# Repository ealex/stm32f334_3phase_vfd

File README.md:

# stm32f334_3phase_vfd
stm32f334 3 phase variable frequency drive with STGIB15CH60TS-L module

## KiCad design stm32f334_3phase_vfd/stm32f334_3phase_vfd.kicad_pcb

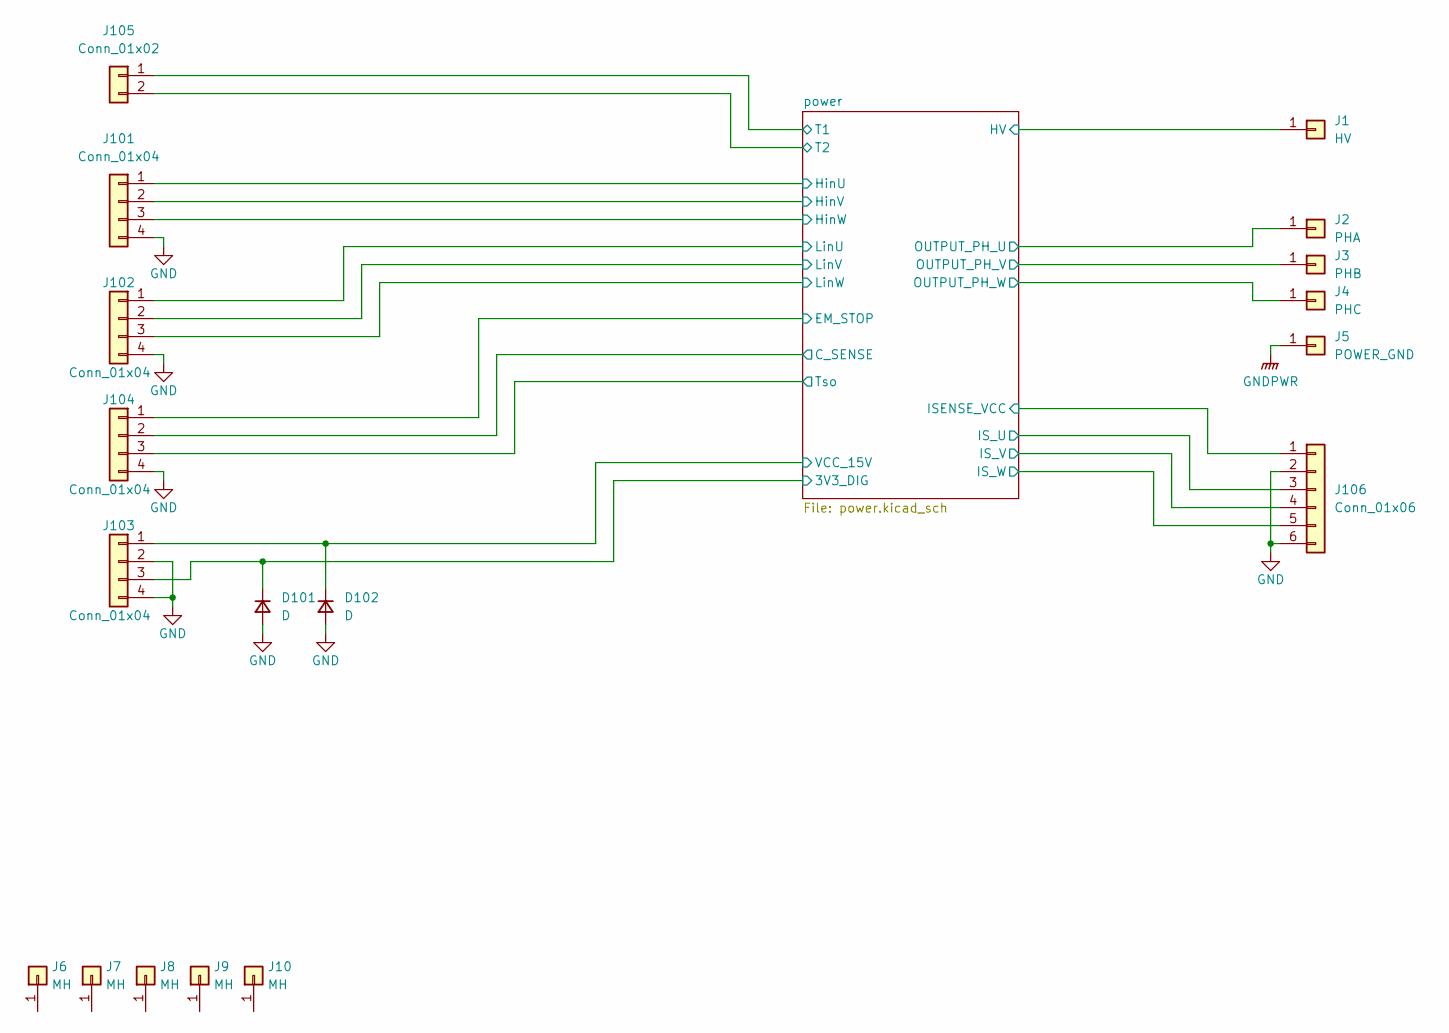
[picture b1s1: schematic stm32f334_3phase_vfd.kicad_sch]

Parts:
D101, D102: D; D_SMA
J1: HV; KEYSTONE_7788
J2: PHA; KEYSTONE_7788
J3: PHB; KEYSTONE_7788
J4: PHC; KEYSTONE_7788
J5: POWER_GND; KEYSTONE_7788
J6, J7, J8, J9, J10: MH; MountingHole_3.2mm_M3_Pad_TopBottom
J101, J102, J103, J104: Conn_01x04; JST_PH_B4B-PH-K_1x04_P2.00mm_Vertical
J105: Conn_01x02; JST_PH_B2B-PH-K_1x02_P2.00mm_Vertical
J106: Conn_01x06; JST_PH_B6B-PH-K_1x06_P2.00mm_Vertical

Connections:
/power/3V3_DIG: D101.1 (K), J103.3; also elsewhere on the board
/power/Cin: J104.2; also elsewhere on the board
/power/HV: J1.1; also elsewhere on the board
/power/HinU: J101.1; also elsewhere on the board
/power/HinV: J101.2; also elsewhere on the board
/power/HinW: J101.3; also elsewhere on the board
/power/ISENSE_VCC: J106.1; also elsewhere on the board
/power/IS_U: J106.3; also elsewhere on the board
/power/IS_V: J106.4; also elsewhere on the board
/power/IS_W: J106.5; also elsewhere on the board
/power/LinU: J102.1; also elsewhere on the board
/power/LinV: J102.2; also elsewhere on the board
/power/LinW: J102.3; also elsewhere on the board
/power/T1: J105.1; also elsewhere on the board
/power/T2: J105.2; also elsewhere on the board
/power/Tso: J104.3; also elsewhere on the board
/power/U: J2.1; also elsewhere on the board
/power/V: J3.1; also elsewhere on the board
/power/VCC_15V: D102.1 (K), J103.1; also elsewhere on the board
/power/W: J4.1; also elsewhere on the board
/power/~sd_od: J104.1; also elsewhere on the board
GND: D101.2 (A), D102.2 (A), J101.4, J102.4, J103.2, J103.4, J104.4, J106.2, J106.6; also elsewhere on the board
GNDPWR: J5.1; also elsewhere on the board

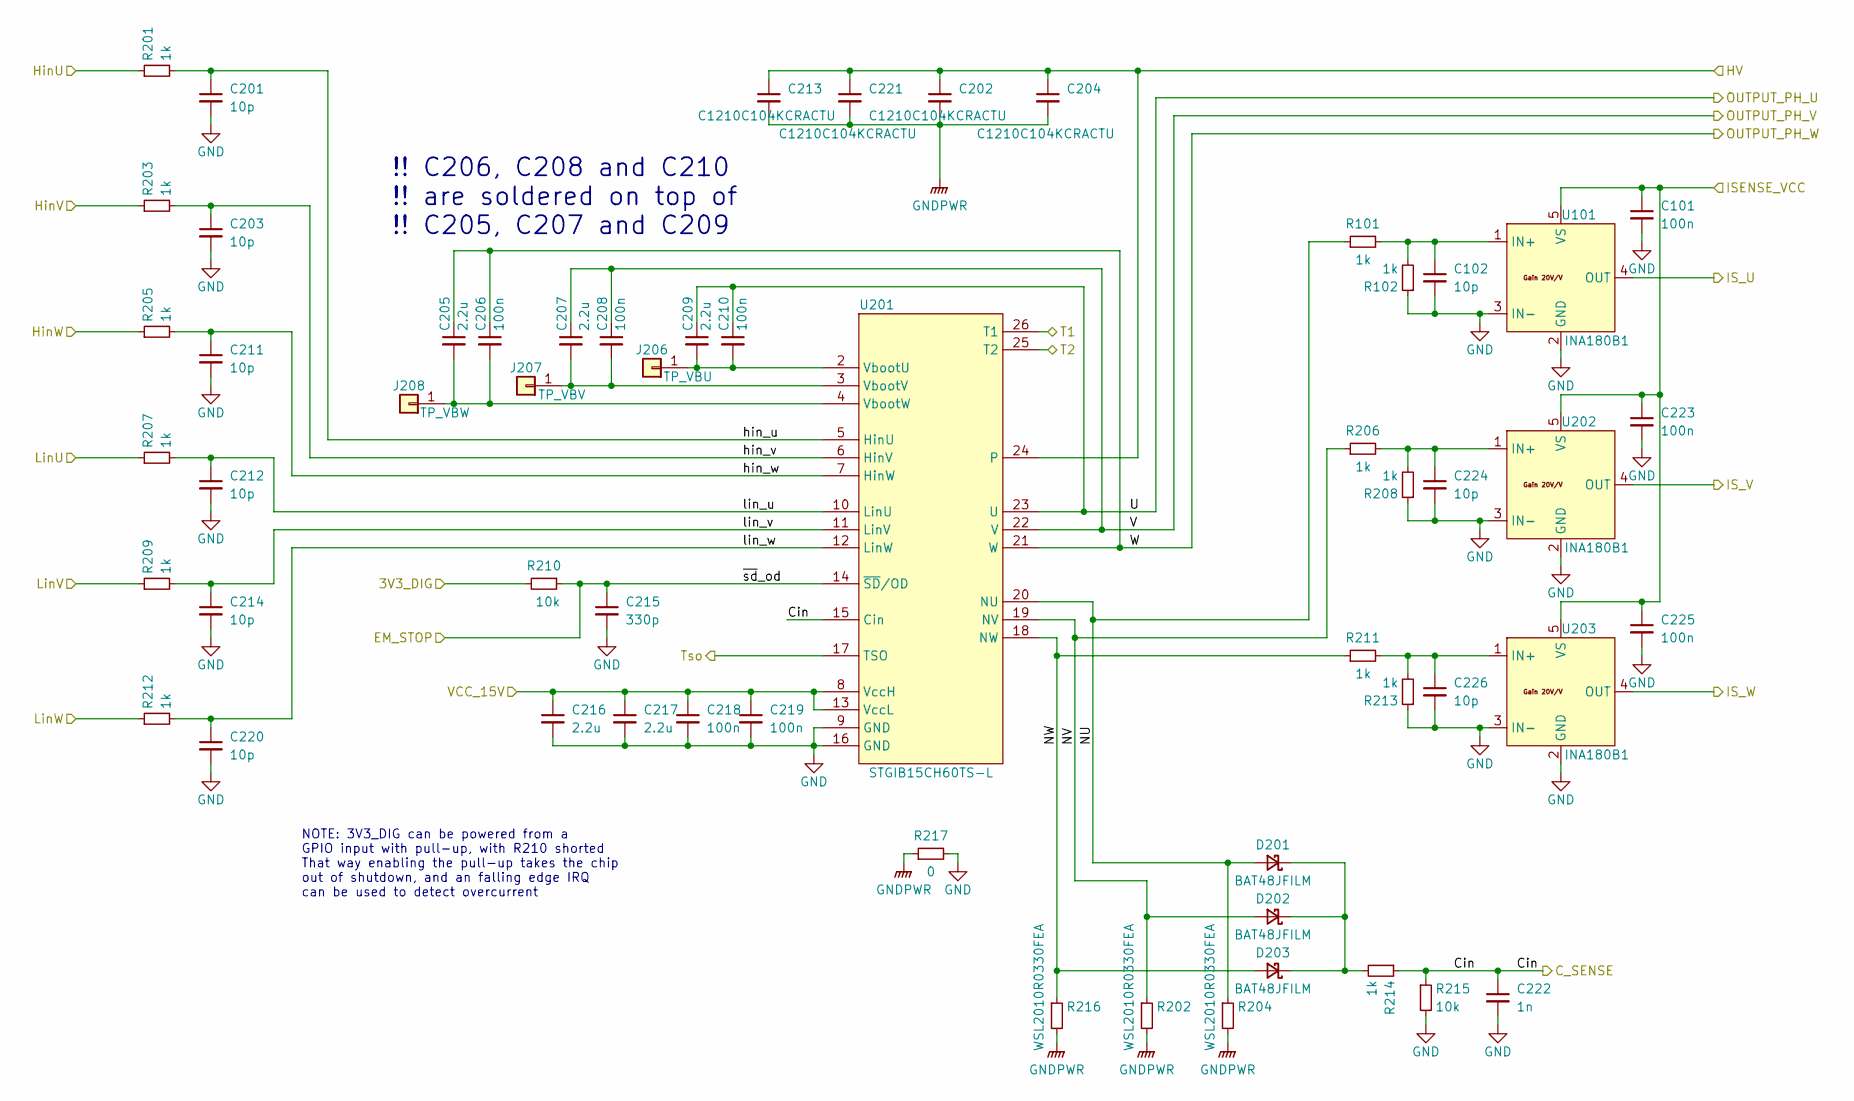
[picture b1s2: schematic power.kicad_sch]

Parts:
C101, C218, C219, C223, C225: 100n; C_0805_2012Metric
C102, C201, C203, C211, C212, C214, C220, C224, C226: 10p; C_0805_2012Metric
C202, C204, C213, C221: C1210C104KCRACTU; C_1210_3225Metric
C205, C207, C209, C216, C217: 2.2u; C_1206_3216Metric
C206, C208, C210: 100n; C_1206_3216Metric
C215: 330p; C_0805_2012Metric
C222: 1n; C_0805_2012Metric
D201, D202, D203: BAT48JFILM; D_SOD-323
J206: TP_VBU; PinHeader_1x01_P2.54mm_Vertical
J207: TP_VBV; PinHeader_1x01_P2.54mm_Vertical
J208: TP_VBW; PinHeader_1x01_P2.54mm_Vertical
R101, R102, R201, R203, R205, R206, R207, R208, R209, R211, R212, R213, R214: 1k; R_0805_2012Metric
R202, R204, R216: WSL2010R0330FEA; R_2010_5025Metric
R210, R215: 10k; R_0805_2012Metric
R217: 0; R_0805_2012Metric
U101, U202, U203: INA180B1; SOT-23-5
U201: STGIB15CH60TS-L; SDIP2B-26L_L1_STM

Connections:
/power/3V3_DIG: R210.2; also elsewhere on the board
/power/Cin: C222.1, R214.1, R215.1, U201.15 (Cin); also elsewhere on the board
/power/HV: C202.1, C204.1, C213.1, C221.1, U201.24; also elsewhere on the board
/power/HinU: R201.1; also elsewhere on the board
/power/HinV: R203.1; also elsewhere on the board
/power/HinW: R205.1; also elsewhere on the board
/power/ISENSE_VCC: C101.1, C223.1, C225.1, U101.5 (VS), U202.5 (VS), U203.5 (VS); also elsewhere on the board
/power/IS_U: U101.4 (OUT); also elsewhere on the board
/power/IS_V: U202.4 (OUT); also elsewhere on the board
/power/IS_W: U203.4 (OUT); also elsewhere on the board
/power/LinU: R207.1; also elsewhere on the board
/power/LinV: R209.1; also elsewhere on the board
/power/LinW: R212.1; also elsewhere on the board
/power/NU: D201.2 (A), R101.1, R204.1, U201.20 (NU)
/power/NV: D202.2 (A), R202.1, R206.1, U201.19 (NV)
/power/NW: D203.2 (A), R211.1, R216.1, U201.18 (NW)
/power/T1: U201.26 (T1); also elsewhere on the board
/power/T2: U201.25 (T2); also elsewhere on the board
/power/Tso: U201.17 (TSO); also elsewhere on the board
/power/U: C209.1, C210.1, U201.23 (U); also elsewhere on the board
/power/V: C207.1, C208.1, U201.22 (V); also elsewhere on the board
/power/VCC_15V: C216.1, C217.1, C218.1, C219.1, U201.8 (VccH), U201.13 (VccL); also elsewhere on the board
/power/W: C205.1, C206.1, U201.21 (W); also elsewhere on the board
/power/hin_u: C201.1, R201.2, U201.5 (HinU)
/power/hin_v: C203.1, R203.2, U201.6 (HinV)
/power/hin_w: C211.1, R205.2, U201.7 (HinW)
/power/lin_u: C212.1, R207.2, U201.10 (LinU)
/power/lin_v: C214.1, R209.2, U201.11 (LinV)
/power/lin_w: C220.1, R212.2, U201.12 (LinW)
/power/~sd_od: C215.1, R210.1, U201.14 (~SD/OD); also elsewhere on the board
GND: C101.2, C102.2, C201.2, C203.2, C211.2, C212.2, C214.2, C215.2, C216.2, C217.2, C218.2, C219.2, C220.2, C222.2, C223.2, C224.2, C225.2, C226.2, R102.1, R208.1, R213.1, R215.2, R217.2, U101.2 (GND), U101.3 (IN-), U201.9 (GND), U201.16 (GND), U202.2 (GND), U202.3 (IN-), U203.2 (GND), U203.3 (IN-); also elsewhere on the board
GNDPWR: C202.2, C204.2, C213.2, C221.2, R202.2, R204.2, R216.2, R217.1; also elsewhere on the board
unnamed: C102.1, R101.2, R102.2, U101.1 (IN+)
unnamed: C205.2, C206.2, J208.1, U201.4 (VbootW)
unnamed: C207.2, C208.2, J207.1, U201.3 (VbootV)
unnamed: C209.2, C210.2, J206.1, U201.2 (VbootU)
unnamed: C224.1, R206.2, R208.2, U202.1 (IN+)
unnamed: C226.1, R211.2, R213.2, U203.1 (IN+)
unnamed: D201.1 (K), D202.1 (K), D203.1 (K), R214.2

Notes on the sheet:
NOTE: 3V3_DIG can be powered from a GPIO input with pull-up, with R210 shorted That way enabling the pull-up takes the chip out of shutdown, and an falling edge IRQ can be used to detect overcurrent
!! C206, C208 and C210 !! are soldered on top of !! C205, C207 and C209

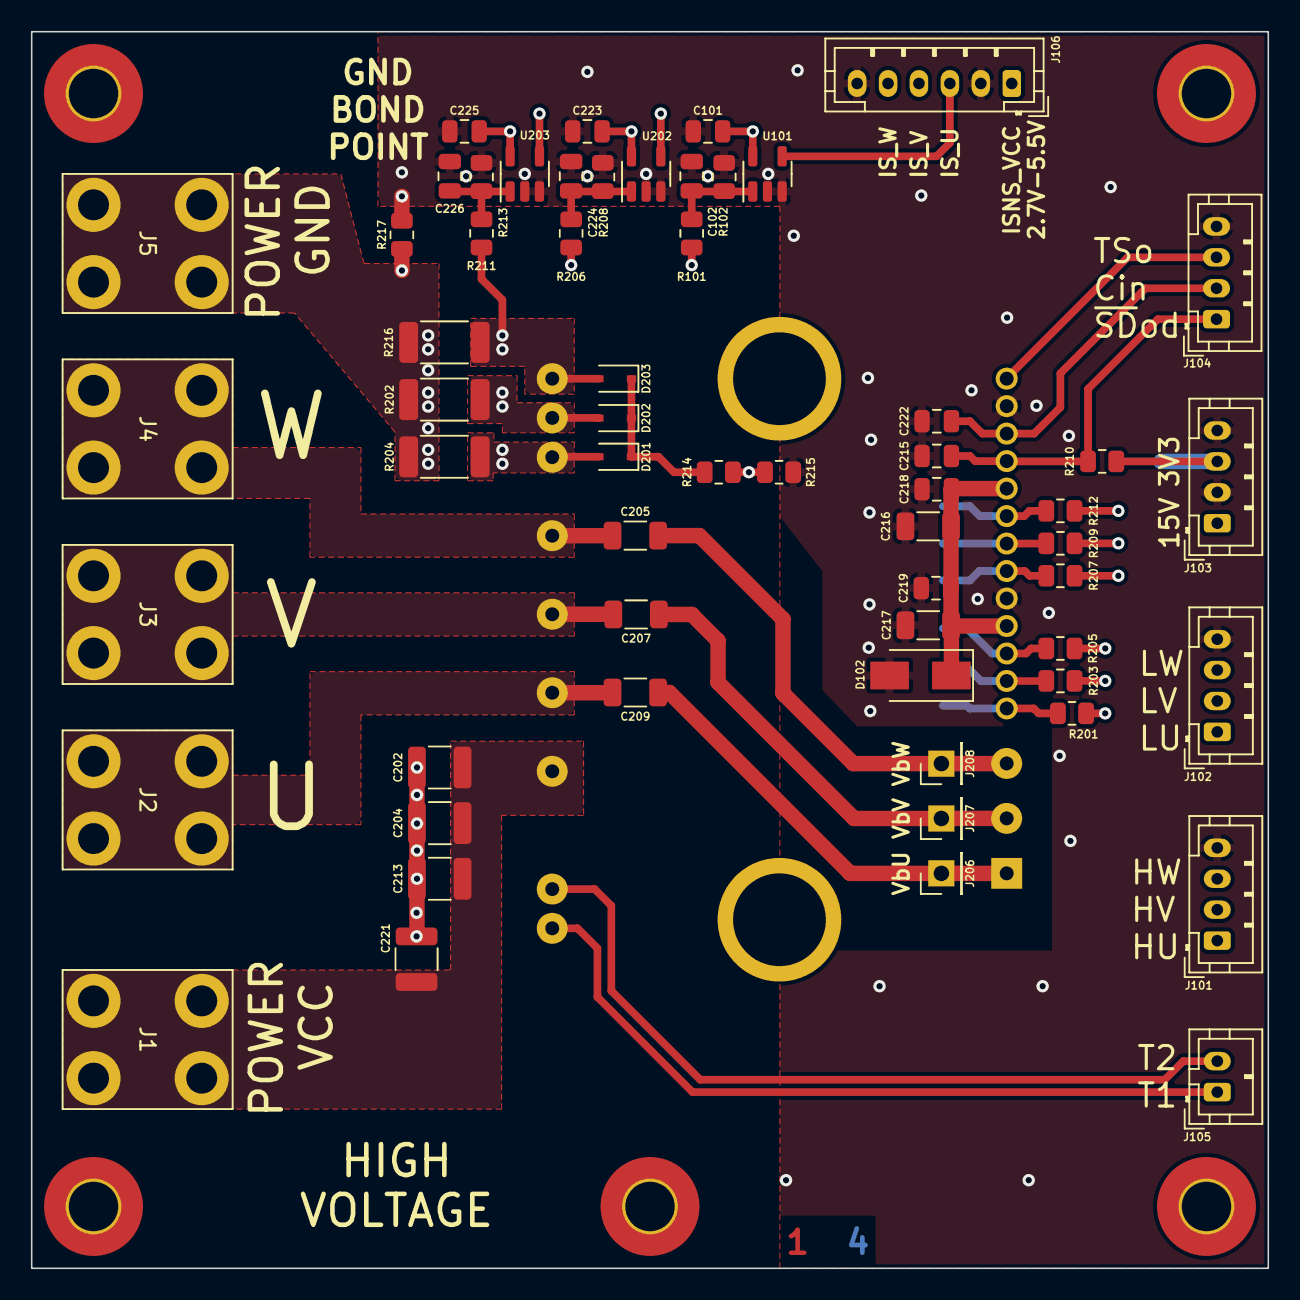
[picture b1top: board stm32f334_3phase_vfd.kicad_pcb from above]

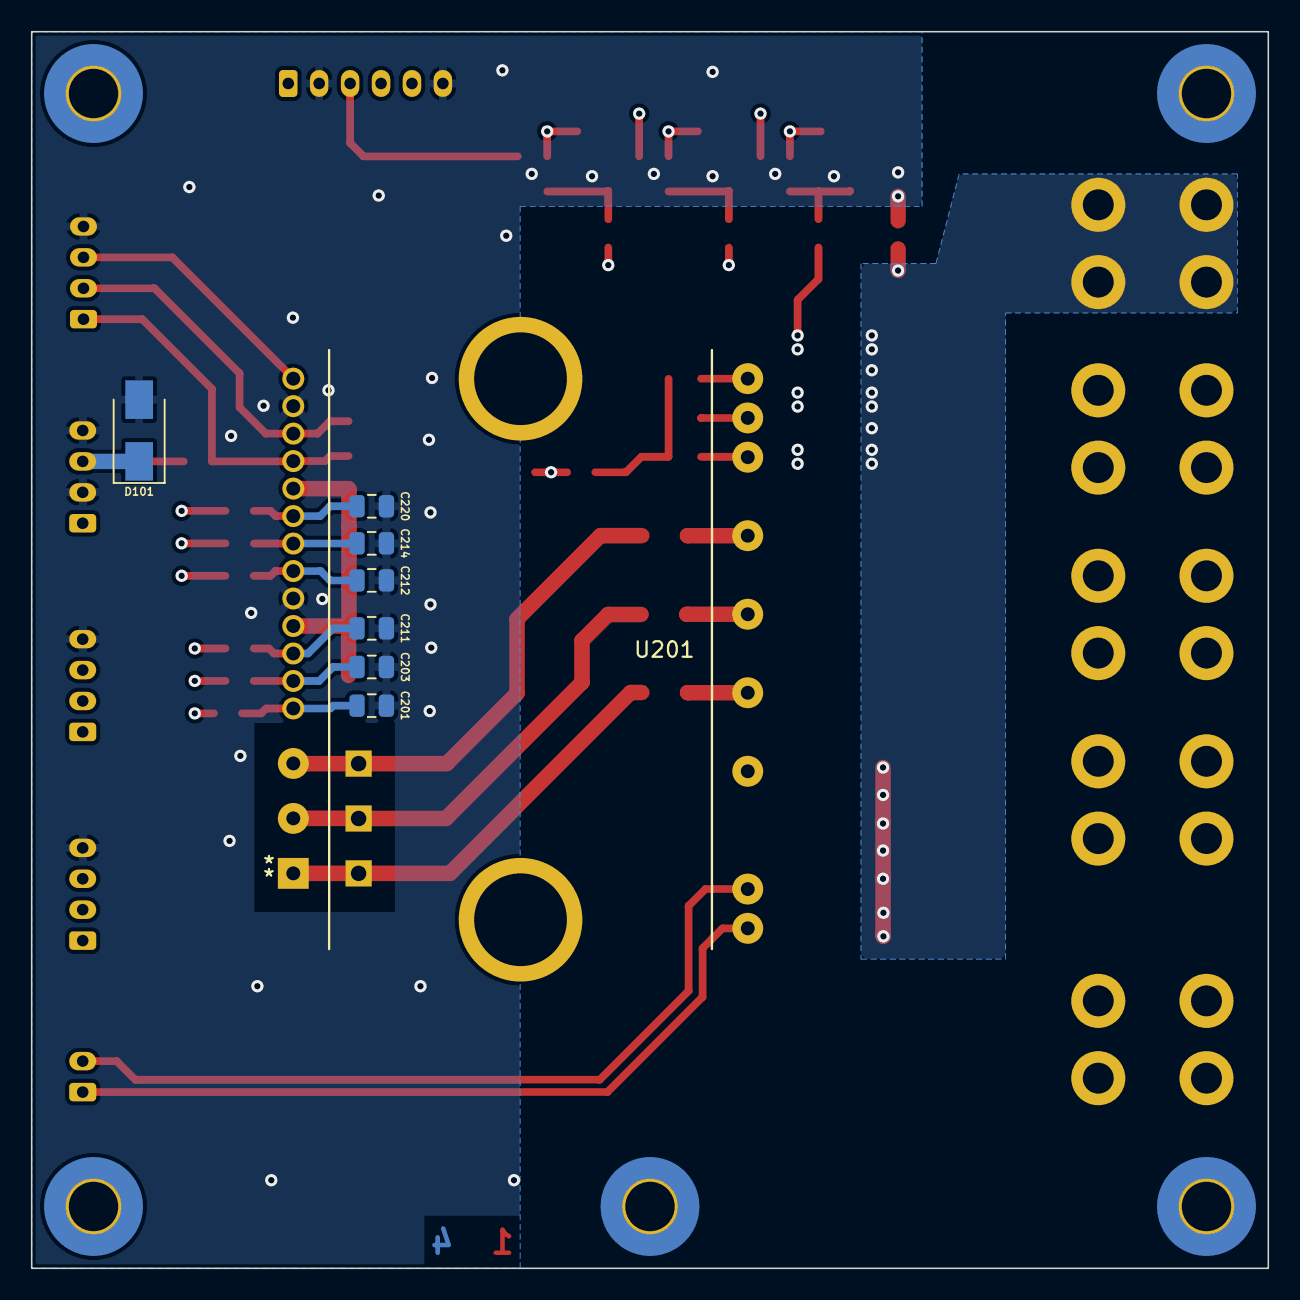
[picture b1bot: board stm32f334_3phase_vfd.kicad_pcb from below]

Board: 4 copper layers, 80.0 x 80.0 mm, 72 parts (8 on the bottom side), 39 nets.

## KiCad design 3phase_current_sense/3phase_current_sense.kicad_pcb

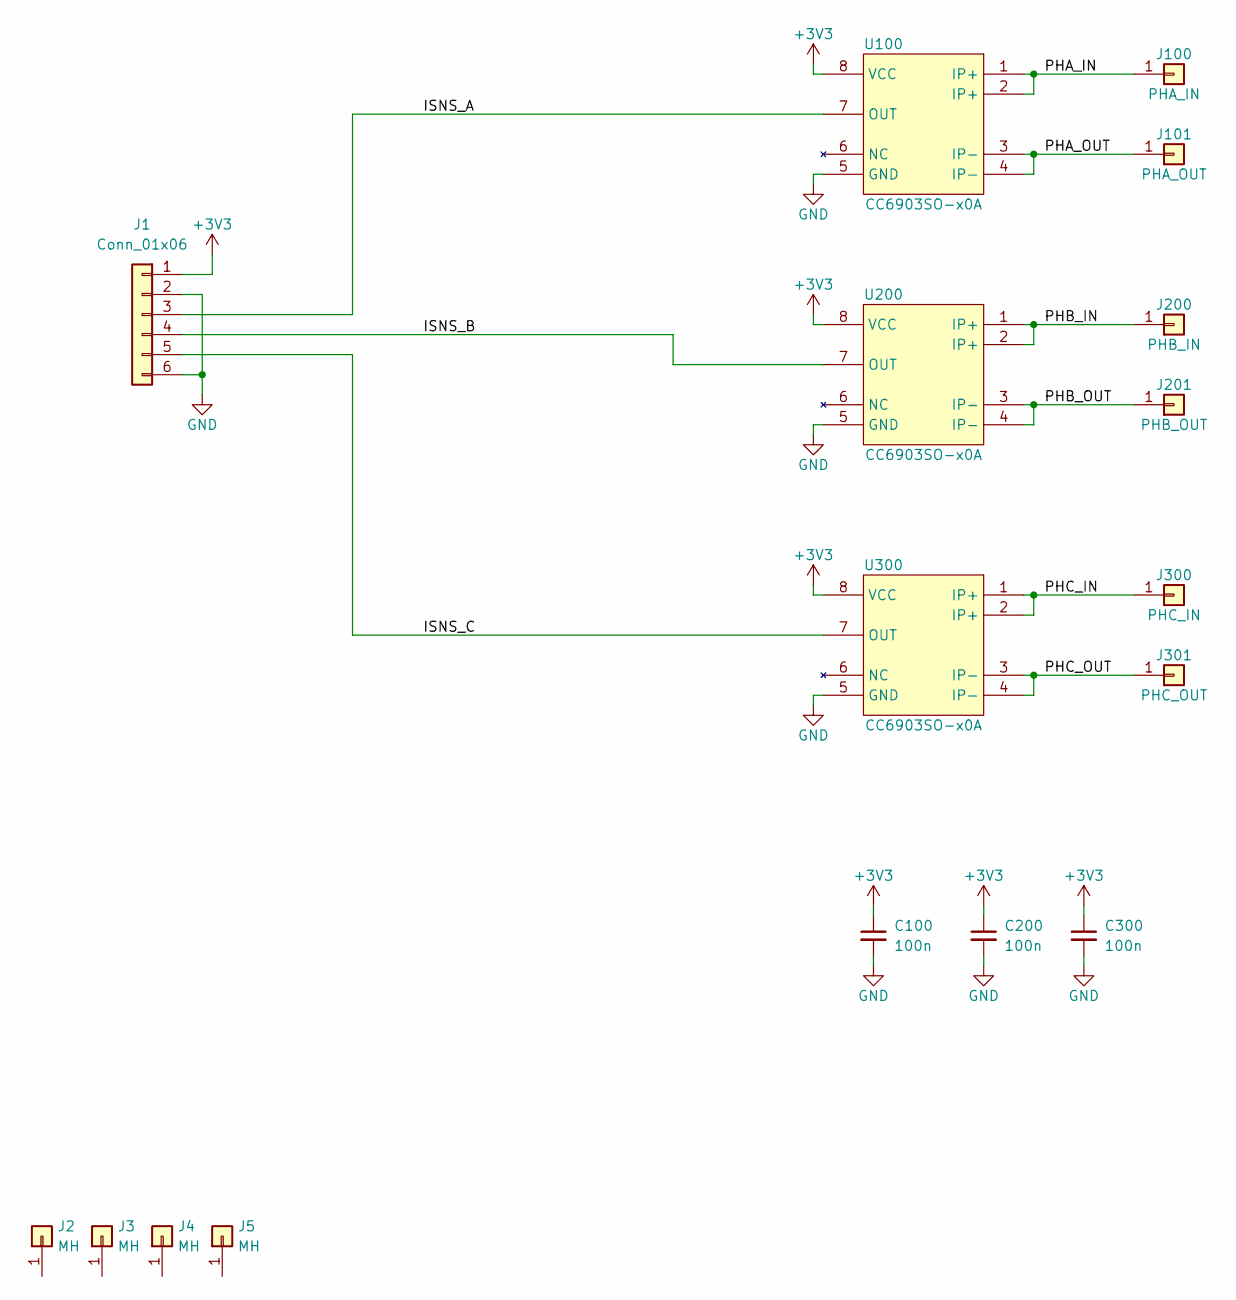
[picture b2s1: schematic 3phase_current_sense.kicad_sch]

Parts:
C100, C200, C300: 100n; C_1206_3216Metric
J1: Conn_01x06; JST_PH_B6B-PH-K_1x06_P2.00mm_Vertical
J2, J3, J4, J5: MH; MountingHole_3.2mm_M3_Pad_TopBottom
J100: PHA_IN; 1904969
J101: PHA_OUT; 1904969
J200: PHB_IN; 1904969
J201: PHB_OUT; 1904969
J300: PHC_IN; 1904969
J301: PHC_OUT; 1904969
U100, U200, U300: CC6903SO-x0A; SO-8_3.9x4.9mm_P1.27mm

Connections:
+3V3: C100.1, C200.1, C300.1, J1.1, U100.8 (VCC), U200.8 (VCC), U300.8 (VCC)
/ISNS_A: J1.3, U100.7 (OUT)
/ISNS_B: J1.4, U200.7 (OUT)
/ISNS_C: J1.5, U300.7 (OUT)
/PHA_IN: J100.1, U100.1 (IP+), U100.2 (IP+)
/PHA_OUT: J101.1, U100.3 (IP-), U100.4 (IP-)
/PHB_IN: J200.1, U200.1 (IP+), U200.2 (IP+)
/PHB_OUT: J201.1, U200.3 (IP-), U200.4 (IP-)
/PHC_IN: J300.1, U300.1 (IP+), U300.2 (IP+)
/PHC_OUT: J301.1, U300.3 (IP-), U300.4 (IP-)
GND: C100.2, C200.2, C300.2, J1.2, J1.6, U100.5 (GND), U200.5 (GND), U300.5 (GND)

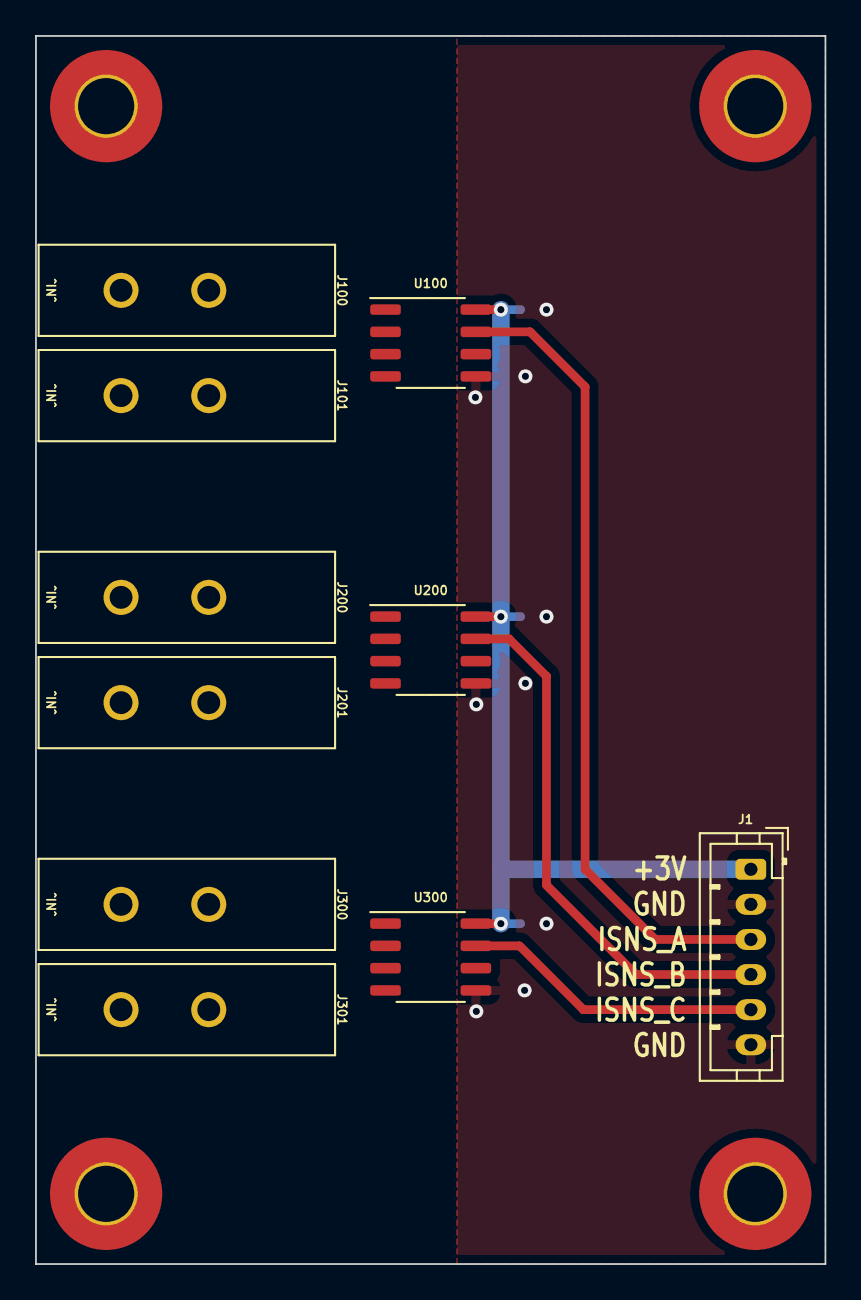
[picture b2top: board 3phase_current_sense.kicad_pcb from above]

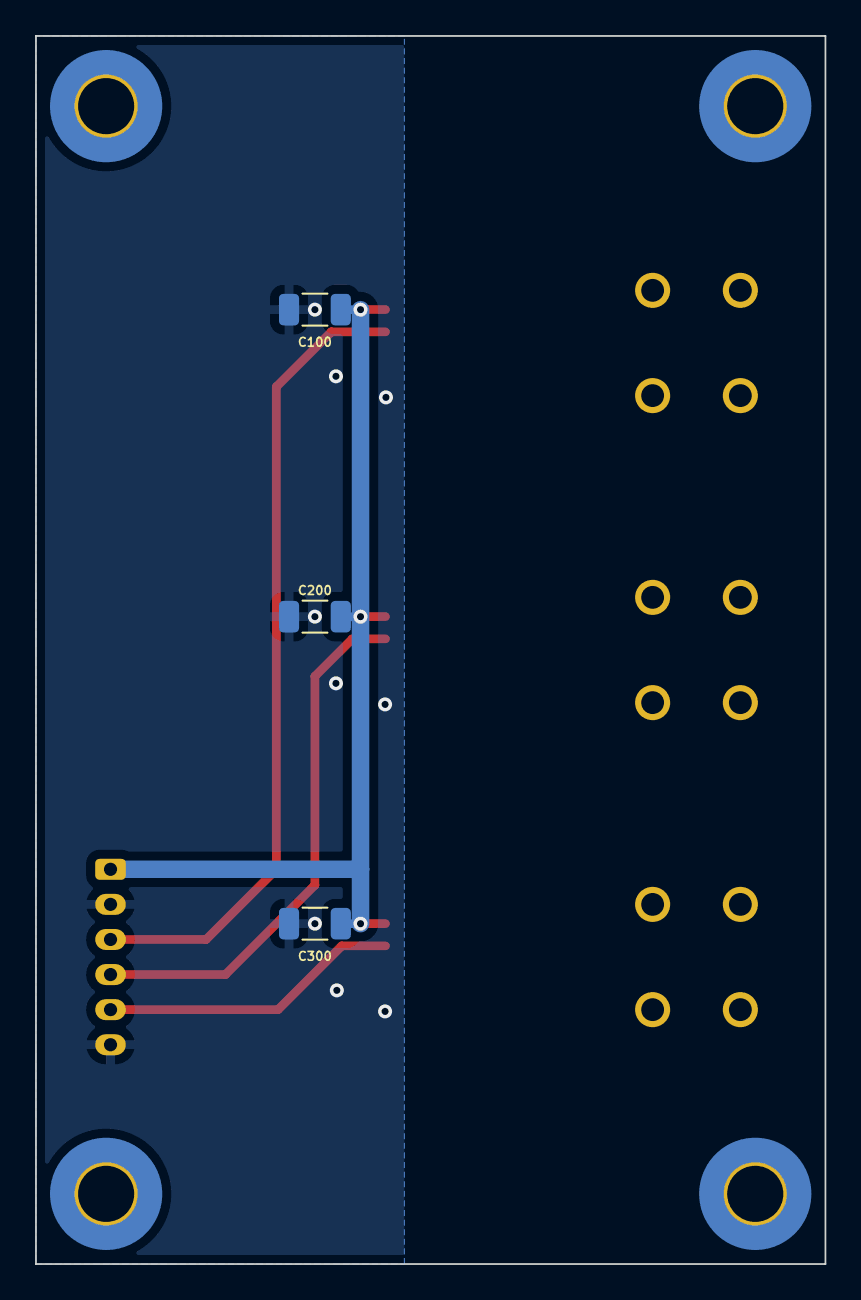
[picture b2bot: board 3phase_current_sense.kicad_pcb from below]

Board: 2 copper layers, 45.0 x 70.0 mm, 17 parts (3 on the bottom side), 11 nets.

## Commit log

2024-04-26 add components documentation
2024-04-26 start kicad project
2024-04-28 update documentation
2024-04-28 continue schematic work
2024-04-28 update schematic
2024-04-28 power connector docs
2024-05-01 update schematic, start power section layout
2024-05-06 add board for 3 phase current measurement
2024-05-06 move 3 phase current sensors on a new board, allow for the current sense board to be stacked
2024-05-10 switch to LQFP48 cpu, continue workin on layout
2024-05-12 schematic update
2025-01-27 pcb fix and schematic clean-up
2025-02-01 upodate docs
2025-07-01 remove unrequired docs
2025-07-01 small updates in the schematic
2025-07-01 start working on the source code
2025-07-01 update schematic pdf
